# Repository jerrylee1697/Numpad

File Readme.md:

# Numpad Project

## Render Version 1.1

## Parts
| Part  | Link |
| --------------- | -------------- |
| MCU             | STM32F4XX      |
| Oled Screen     | [ER-OLED022-1Y](https://www.buydisplay.com/yellow-2-2-inch-128x32-oled-module-manufacturer-serial-spi-ssd1305)  |
| Rotary Encoder  | [M274](https://www.probotronix.com/product/m274-360-degree-rotary-encoder-module-brick-sensor/)           |
| Type-C Port     | Not Selected   |

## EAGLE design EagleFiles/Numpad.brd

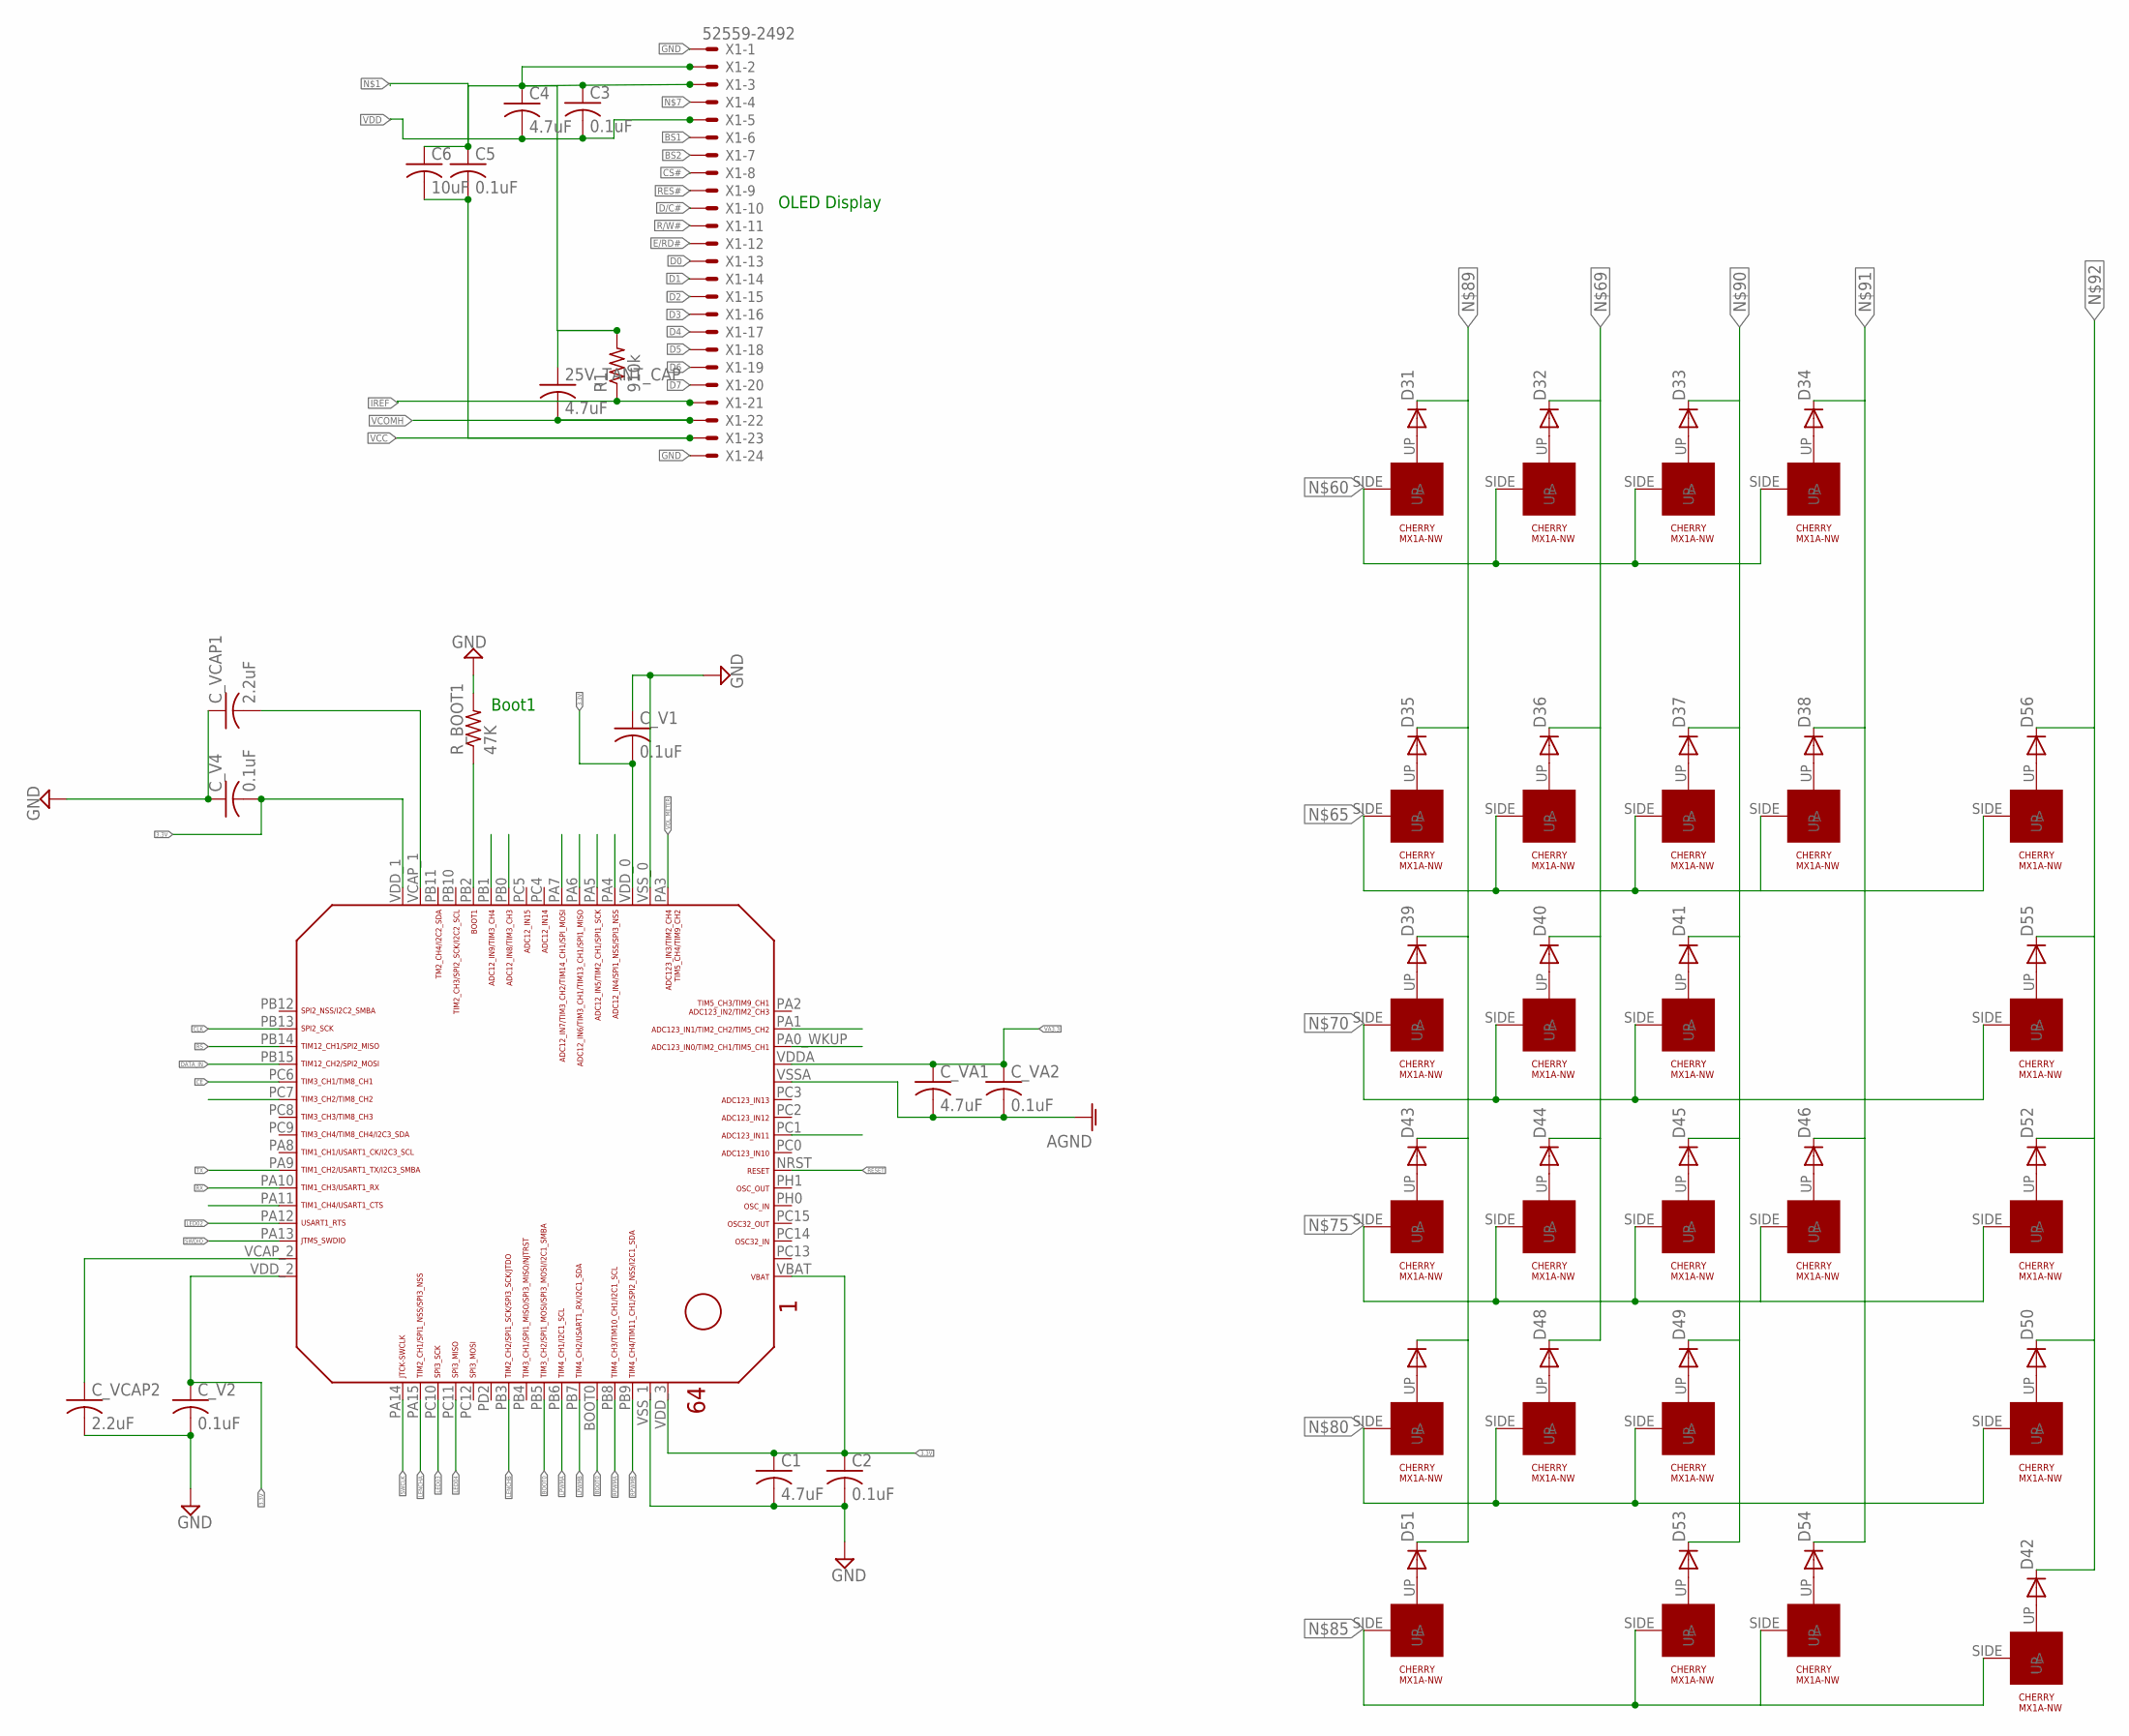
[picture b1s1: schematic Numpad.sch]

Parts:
25V_TANT_CAP: 4.7uF; C0805
C1, C4: 4.7uF; C0603
C2, C3, C5: 0.1uF; C0603
C6: 10uF; C0603
C_V1, C_V2, C_V4: 0.1uF; C0603
C_VA1: 4.7uF; C0603
C_VA2: 0.1uF; C0603
C_VCAP1, C_VCAP2: 2.2uF; C0603
D31, D32, D33, D34, D35, D36, D37, D38, D39, D40, D41, D42, D43, D44, D45, D46, D47, D48, D49, D50, D51, D52, D53, D54, D55, D56: 1N4148DO35-7; DO35-7
R1: 910k; R0603
R_BOOT1: 47K; R0603
U$31, U$36, U$37, U$38, U$39, U$40, U$41, U$42, U$43, U$44, U$45, U$46, U$47, U$48, U$49, U$50, U$51, U$52, U$53, U$54, U$55, U$56, U$57, U$58, U$59, U$60: CHERRY-MX1A-E1NW; CHERRYMX-NN
U$35: STM32F405/415_LQFP64
X1: 52559-2492

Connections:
3.3V: C1.1, C2.1, C_V1.2, C_V2.1, C_V4.2, U$35.VBAT, U$35.VDD_0, U$35.VDD_1, U$35.VDD_2, U$35.VDD_3
AGND: C_VA1.2, C_VA2.2, U$35.VSSA
BOOT0: U$35.BOOT0, U$35.PB5
BS1: X1.6
BS2: X1.7
BUZZER: U$35.PA6
CE: U$35.PC6
CLK: U$35.PB13
CS#: X1.8
D0: X1.13
D1: X1.14
D2: X1.15
D3: X1.16
D4: X1.17
D5: X1.18
D6: X1.19
D7: X1.20
D/C#: X1.10
DATA_IN: U$35.PB15
DIAGONAL_EMITTER: U$35.PA7
E/RD#: X1.12
GND: C1.2, C2.2, C_V1.1, C_V2.2, C_V4.1, C_VCAP1.1, C_VCAP2.2, R_BOOT1.2, U$35.VSS_0, U$35.VSS_1, X1.1, X1.24
IREF: R1.1, X1.21
LED01: U$35.PA11
LED02: U$35.PA12
LED03: U$35.PC10
LED04: U$35.PC11
LENCHA: U$35.PA15
LENCHB: U$35.PB3
LF_EMITTER: U$35.PC7
LF_RECEIVER: U$35.PB1
LPWMA: U$35.PB6
LPWMB: U$35.PB7
L_RECEIVER: U$35.PB0
unnamed: R_BOOT1.1, U$35.PB2
unnamed: D31.A, U$31.UP
unnamed: C_VCAP1.2, U$35.VCAP_1
unnamed: C_VCAP2.1, U$35.VCAP_2
unnamed: D32.A, U$36.UP
unnamed: D33.A, U$37.UP
unnamed: D34.A, U$38.UP
unnamed: U$31.SIDE (A), U$36.SIDE (A), U$37.SIDE (A), U$38.SIDE (A)
unnamed: D35.A, U$39.UP
unnamed: D36.A, U$40.UP
unnamed: D37.A, U$41.UP
unnamed: D38.A, U$42.UP
unnamed: U$39.SIDE (A), U$40.SIDE (A), U$41.SIDE (A), U$42.SIDE (A), U$60.SIDE (A)
unnamed: D39.A, U$43.UP
unnamed: D40.A, U$44.UP
unnamed: D41.A, U$45.UP
unnamed: D32.C, D36.C, D40.C, D44.C, D48.C
unnamed: U$43.SIDE (A), U$44.SIDE (A), U$45.SIDE (A), U$59.SIDE (A)
unnamed: D43.A, U$47.UP
unnamed: D44.A, U$48.UP
unnamed: D45.A, U$49.UP
unnamed: D46.A, U$50.UP
unnamed: U$47.SIDE (A), U$48.SIDE (A), U$49.SIDE (A), U$50.SIDE (A), U$56.SIDE (A)
unnamed: D47.A, U$51.UP
unnamed: D48.A, U$52.UP
unnamed: D49.A, U$53.UP
unnamed: D42.A, U$46.UP
unnamed: U$51.SIDE (A), U$52.SIDE (A), U$53.SIDE (A), U$54.SIDE (A)
unnamed: D51.A, U$55.UP
unnamed: D50.A, U$54.UP
unnamed: D53.A, U$57.UP
unnamed: D54.A, U$58.UP
unnamed: U$46.SIDE (A), U$55.SIDE (A), U$57.SIDE (A), U$58.SIDE (A)
unnamed: D52.A, U$56.UP
unnamed: D55.A, U$59.UP
unnamed: D56.A, U$60.UP
unnamed: D31.C, D35.C, D39.C, D43.C, D47.C, D51.C
unnamed: D33.C, D37.C, D41.C, D45.C, D49.C, D53.C
unnamed: D34.C, D38.C, D46.C, D54.C
unnamed: D42.C, D50.C, D52.C, D55.C, D56.C
R/W#: X1.11
RENCHA: U$35.PA0_WKUP (PA0_AKUP)
RENCHB: U$35.PA1
RES#: X1.9
RESET: U$35.NRST
RF_EMITTER: U$35.PC1
RF_RECEIVER: U$35.PA4
RPWMA: U$35.PB8
RPWMB: U$35.PB9
RS: U$35.PB14
RX: U$35.PA10
R_RECEIVER: U$35.PA5
SWCLK: U$35.PA14
SWDIO: U$35.PA13
TX: U$35.PA9
VA3.3: C_VA1.1, C_VA2.1, U$35.VDDA
VCC: C5.2, C6.2, X1.23
VCOMH: 25V_TANT_CAP.2, X1.22
VDD: C3.2, C4.2, X1.5
VLSS: 25V_TANT_CAP.1, C3.1, C4.1, C5.1, C6.1, R1.2, X1.2, X1.3
VOL_METER: U$35.PA3

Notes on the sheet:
Boot1
OLED Display

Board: 2 copper layers, 70 parts (0 on the bottom side), 50 nets, no tracks yet.

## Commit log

2020-06-10 Basic key layout in sch
2020-06-10 Render 1.1
2020-06-10 Readme added
2020-06-10 New renders
2020-06-10 Oled schematic added
